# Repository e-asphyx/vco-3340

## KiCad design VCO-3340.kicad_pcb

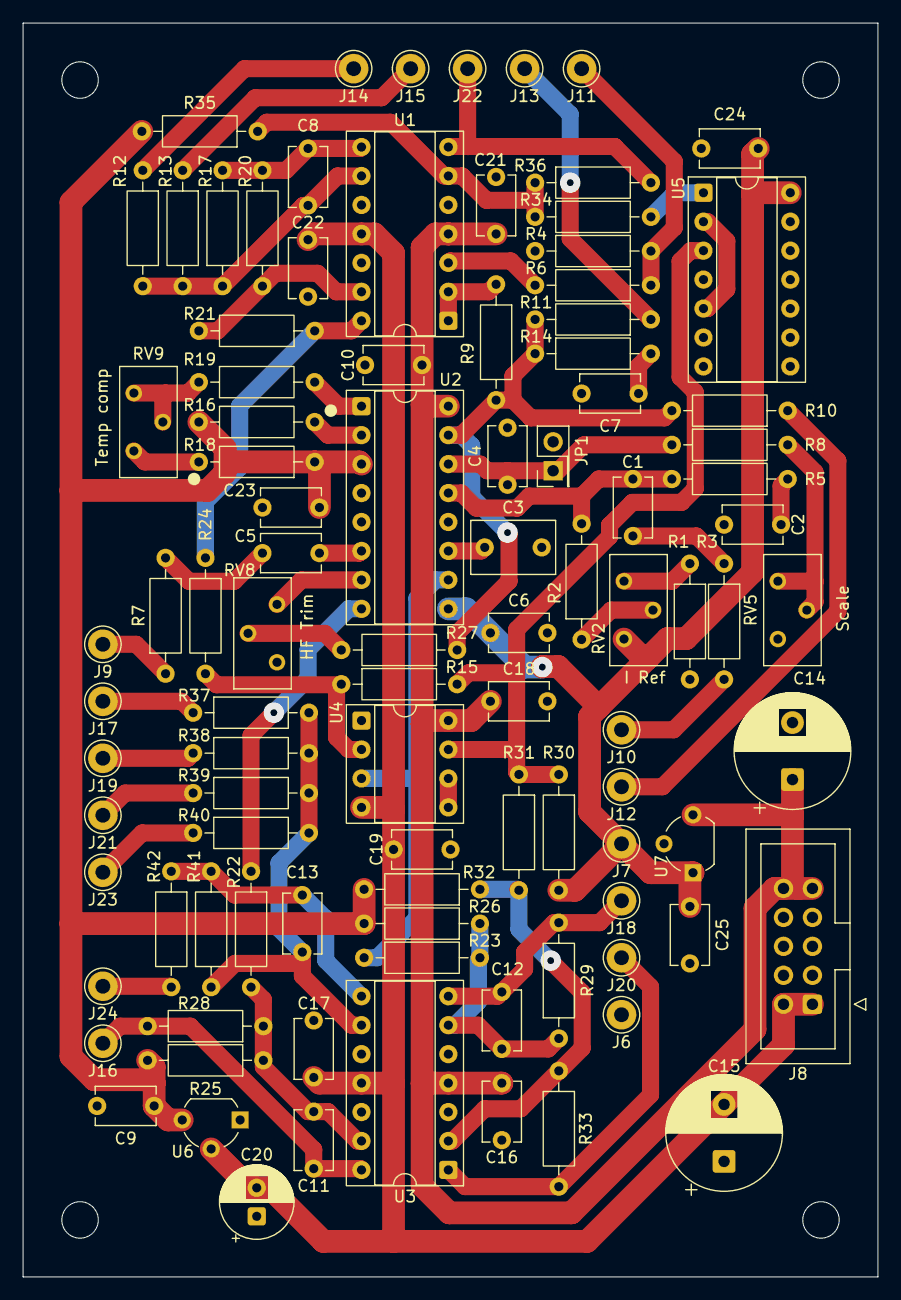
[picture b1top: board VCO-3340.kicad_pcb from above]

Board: 2 copper layers, 75.0 x 110.0 mm, 102 parts (0 on the bottom side), 58 nets.

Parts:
C1: 100n; C_Disc_D5.1mm_W3.2mm_P5.00mm
C2, C7: 10n; C_Disc_D5.1mm_W3.2mm_P5.00mm
C3: 1n 1%; C_Rect_L7.2mm_W4.5mm_P5.00mm_FKS2_FKP2_MKS2_MKP2
C4: 560p; C_Disc_D5.1mm_W3.2mm_P5.00mm
C5: 1n; C_Disc_D5.1mm_W3.2mm_P5.00mm
C6, C9, C10, C16, C17, C18, C19, C21, C22, C23, C24, C25: 0.1u; C_Disc_D5.1mm_W3.2mm_P5.00mm
C8, C11, C12: 100p; C_Disc_D5.1mm_W3.2mm_P5.00mm
C13: 22p; C_Disc_D5.1mm_W3.2mm_P5.00mm
C14, C15: 100u; CP_Radial_D10.0mm_P5.00mm
C20: 1u; CP_Radial_D6.3mm_P2.50mm
H1, H2, H3, H4: MountingHole; MountingHole_3.2mm_M3
J6, J7, J9, J10, J11, J12, J13, J14, J15, J16, J17, J18, J19, J20, J21, J22, J23, J24: Conn_01x01; Pin_D1.3mm_L11.0mm
J8: Conn_02x05_Odd_Even; IDC-Header_2x05_P2.54mm_Vertical
JP1: Jumper_2_Open; PinHeader_2x01_P2.54mm_Vertical
R1, R35, R36: 20k; R_Axial_DIN0207_L6.3mm_D2.5mm_P10.16mm_Horizontal
R2: 750k; R_Axial_DIN0207_L6.3mm_D2.5mm_P10.16mm_Horizontal
R3, R4, R15, R27: 1M; R_Axial_DIN0207_L6.3mm_D2.5mm_P10.16mm_Horizontal
R5, R14: 470; R_Axial_DIN0207_L6.3mm_D2.5mm_P10.16mm_Horizontal
R6, R20, R21, R34: 10k; R_Axial_DIN0207_L6.3mm_D2.5mm_P10.16mm_Horizontal
R7, R24, R30, R42: 1k; R_Axial_DIN0207_L6.3mm_D2.5mm_P10.16mm_Horizontal
R8: 1.6k; R_Axial_DIN0207_L6.3mm_D2.5mm_P10.16mm_Horizontal
R9: 100k 0.1%; R_Axial_DIN0207_L6.3mm_D2.5mm_P10.16mm_Horizontal
R10, R26, R29: 200k; R_Axial_DIN0207_L6.3mm_D2.5mm_P10.16mm_Horizontal
R11: 47k; R_Axial_DIN0207_L6.3mm_D2.5mm_P10.16mm_Horizontal
R12, R13, R17, R22, R23, R25, R28: 100k; R_Axial_DIN0207_L6.3mm_D2.5mm_P10.16mm_Horizontal
R16, R18: 5.6k; R_Axial_DIN0207_L6.3mm_D2.5mm_P10.16mm_Horizontal
R19, R31: 18k; R_Axial_DIN0207_L6.3mm_D2.5mm_P10.16mm_Horizontal
R32, R33: 36k; R_Axial_DIN0207_L6.3mm_D2.5mm_P10.16mm_Horizontal
R37, R38, R39, R40, R41: 12k; R_Axial_DIN0207_L6.3mm_D2.5mm_P10.16mm_Horizontal
RV2: 10k; Potentiometer_Bourns_3296Y_Vertical
RV5: 500; Potentiometer_Bourns_3296Y_Vertical
RV8: 20k; Potentiometer_Bourns_3296Y_Vertical
RV9: 5k; Potentiometer_Bourns_3296Y_Vertical
U1, U3: TL074; DIP-14_W7.62mm_Socket
U2: AS3340; DIP-16_W7.62mm_Socket
U4: LM311; DIP-8_W7.62mm_Socket
U5: 4013; DIP-14_W7.62mm_Socket
U6: LM79L05_TO92; TO-92_Wide
U7: LM78L05_TO92; TO-92_Wide

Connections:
+5V: C6.1, C24.1, C25.1, J7.1 (Pin_1_1), R30.2, RV2.3, U2.9 (VSSI), U5.14 (VDD), U7.1 (VO)
+12V: C10.1, C14.1, C16.1, C18.1, C21.1, J8.9, J8.10, U1.4 (V+), U2.16 (VCC), U3.4 (V+), U4.8 (V+), U7.3 (VI)
-5V: C9.1, C23.2, R16.1, R18.1, R25.2, R26.2, R32.2, R35.2, U2.3 (VEE), U6.3 (VO)
-12V: C15.2, C17.2, C19.2, C20.2, C22.2, J8.1, J8.2, U1.11 (V-), U3.11 (V-), U4.4 (V-), U6.2 (VI)
/CMP_OUT: R27.2, R30.1, R31.1, U4.7, U5.3 (C)
/CTL_SUM: R9.2, R10.2, R11.2, R14.1, R15.1, U2.15 (VFCI)
/CV_IN: J11.1 (Pin_1_1), R4.2, R6.1
/FM_IN: J10.1 (Pin_1_1), R3.2
/FREQ_COARSE: J13.1 (Pin_1_1), R11.1
/FREQ_FINE: J12.1 (Pin_1_1), R10.1
/HS_IN: C5.2, U2.6 (VHSI)
/I_REF: C1.1, R2.2, R5.1, U2.13 (VLFI)
/MIX_OUT: J24.1 (Pin_1_1), R42.2
/PW_IN: J14.1 (Pin_1_1), R12.1
/PW_W: J15.1 (Pin_1_1), R13.1
/SAW_OUT: C11.2, J16.1 (Pin_1_1), R28.2, U3.14
/SAW_W: J17.1 (Pin_1_1), R37.1
/SO: R22.1, U2.8 (VSO)
/SQ_OUT: J20.1 (Pin_1_1), R33.2, U3.1
/SQ_W: J21.1 (Pin_1_1), R39.1
/SUB_OUT: J22.1 (Pin_1_1), R36.2, U1.7
/SUB_W: J23.1 (Pin_1_1), R40.1
/SYNC_IN: J9.1 (Pin_1_1), R7.1
/TO: R23.1, U2.10 (VTO), U4.3 (-)
/TR_OUT: C12.2, J18.1 (Pin_1_1), R29.2, U3.7
/TR_W: J19.1 (Pin_1_1), R38.1
GND: C2.2, C3.2, C4.2, C6.2, C7.2, C9.2, C10.2, C14.2, C15.1, C16.2, C17.1, C18.2, C19.1, C20.1, C21.2, C22.1, C23.1, C24.2, C25.2, J6.1 (Pin_1_1), J8.3, J8.4, J8.5, J8.6, J8.7, J8.8, JP1.2 (B), R1.2, R4.1, RV5.3, RV8.1, U1.5 (+), U1.10 (+), U1.12 (+), U2.5 (VPWM), U2.12 (GND), U3.3 (+), U3.5 (+), U3.10 (+), U3.12 (+), U4.1 (GND), U5.4 (R), U5.6 (S), U5.7 (VSS), U5.8 (S), U5.9 (D), U5.10 (R), U5.11 (C), U6.1 (GND), U7.2 (GND)
unnamed: C1.2, R3.1
unnamed: C2.1, R5.2
unnamed: C5.1, R7.2
unnamed: C7.1, R14.2
unnamed: C8.2, R17.2, R20.2, U1.8
unnamed: C13.2, R41.2, R42.1, U3.8
unnamed: C4.1, JP1.1 (A), R8.1, U2.14 (VS)
unnamed: R1.1, RV2.1
unnamed: R2.1, RV2.2
unnamed: R8.2, RV5.1, RV5.2
unnamed: R15.2, RV8.2
unnamed: R18.2, RV9.3
unnamed: R19.1, RV9.1, RV9.2
unnamed: R21.1, R24.1, U1.14
unnamed: R6.2, U1.3 (+)
unnamed: R9.1, U1.1, U1.2 (-)
unnamed: R34.2, R35.1, R36.1, U1.6 (-)
unnamed: C8.1, R12.2, R13.2, R17.1, U1.9 (-)
unnamed: R20.1, R21.2, U1.13 (-)
unnamed: C3.1, U2.11 (CAP)
unnamed: R19.2, U2.1 (SCALE1)
unnamed: R16.2, U2.2 (SCALE2)
unnamed: RV8.3, U2.7 (VHFT)
unnamed: R31.2, R32.1, R33.1, U3.2 (-)
unnamed: C12.1, R23.2, R26.1, R29.1, U3.6 (-)
unnamed: C13.1, R37.2, R38.2, R39.2, R40.2, R41.1, U3.9 (-)
unnamed: C11.1, R22.2, R25.1, R28.1, U3.13 (-)
unnamed: R24.2, R27.1, U4.2 (+)
unnamed: U4.5 (BAL), U4.6 (STRB)
unnamed: U5.2 (~Q), U5.5 (D)
unnamed: R34.1, U5.1 (Q)
